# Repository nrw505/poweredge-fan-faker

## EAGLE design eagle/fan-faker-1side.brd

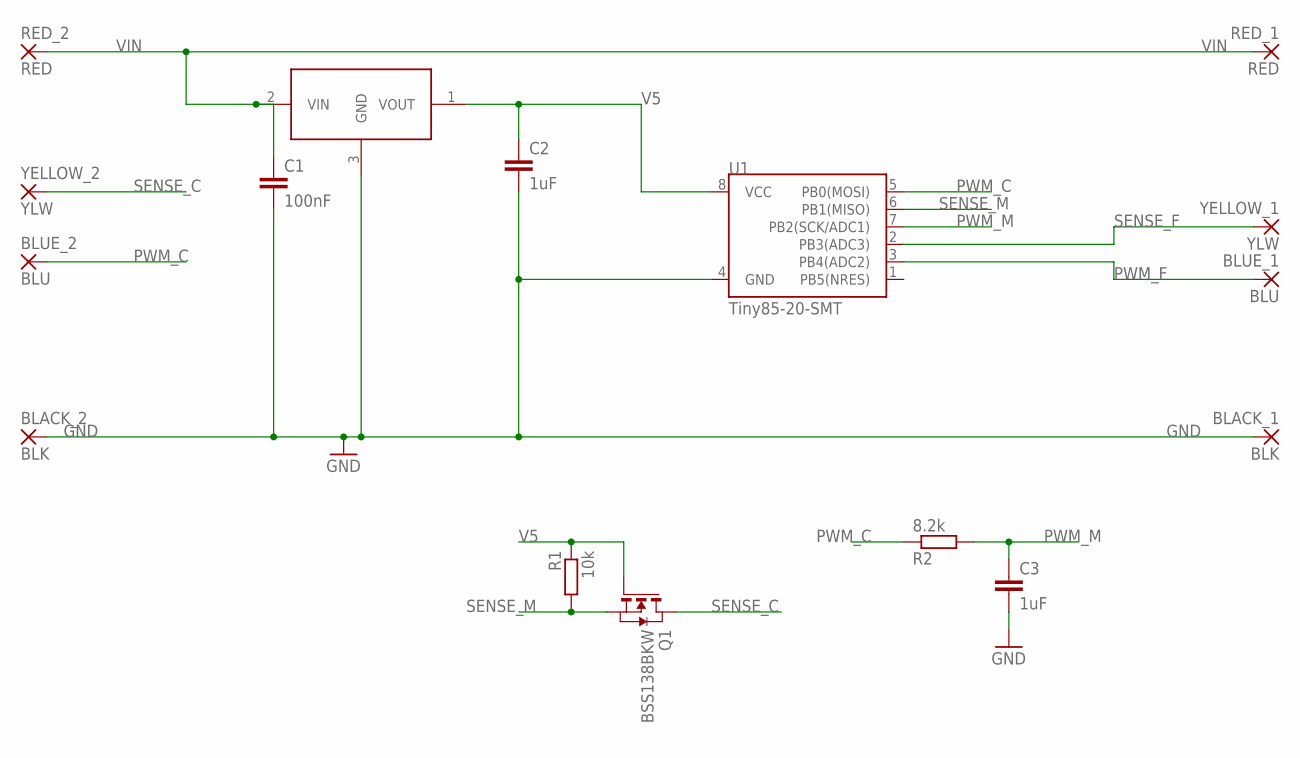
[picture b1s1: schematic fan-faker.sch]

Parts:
BLACK_1, BLACK_2: BLK; 2,54/1,0
BLUE_1, BLUE_2: BLU; 2,54/1,0
C1: 100nF; C0805K
C2, C3: 1uF; C0805K
Q1: BSS138BKW; SOT323
R1: 10k; R0805
R2: 8.2k; R0805
RED_1, RED_2: RED; 2,54/1,0
U1: Tiny85-20-SMT; SO08-EIAJ
U$2: LM3480; SOT23
YELLOW_1, YELLOW_2: YLW; 2,54/1,0

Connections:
GND: BLACK_1.1, BLACK_2.1, C1.2, C2.2, C3.2, U1.4 (GND), U$2.3 (GND)
PWM_C: BLUE_2.1, R2.1, U1.5 (PB0(MOSI))
PWM_F: BLUE_1.1, U1.3 (PB4(ADC2))
PWM_M: C3.1, R2.2, U1.7 (PB2(SCK/ADC1))
SENSE_C: Q1.1 (D), YELLOW_2.1
SENSE_F: U1.2 (PB3(ADC3)), YELLOW_1.1
SENSE_M: Q1.3 (S), R1.2, U1.6 (PB1(MISO))
V5: C2.1, Q1.2 (G), R1.1, U1.8 (VCC), U$2.1 (VOUT)
VIN: C1.1, RED_1.1, RED_2.1, U$2.2 (VIN)

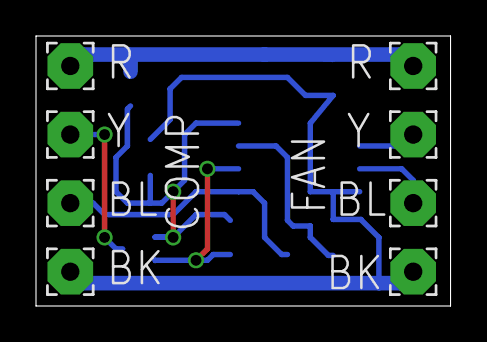
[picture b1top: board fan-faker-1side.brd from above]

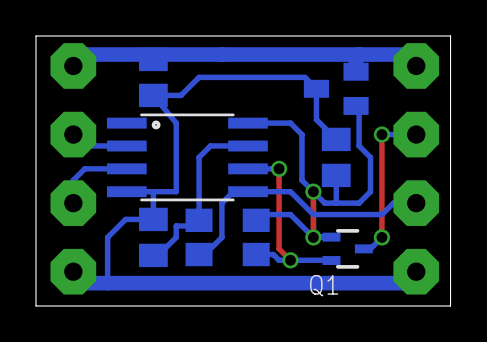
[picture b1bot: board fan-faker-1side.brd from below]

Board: 2 copper layers, 23.0 x 15.0 mm, 16 parts (8 on the bottom side), 9 nets.

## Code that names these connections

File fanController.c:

/* -*- mode: c++; c-basic-offset: 2; -*- */

#include <alloca.h>
#include <string.h>

#include <avr/io.h>
#include <avr/interrupt.h>

// Don't forget to program fuses: this code is expecting the system clock
// to be running at 8 MHz. It was tested on a chip with:
// lfuse=0xe2 hfuse=0xdd efuse=0xff

FUSES = {
  // 8MHz Internal RC Osc., Slow Startup
  .low = (FUSE_SUT0 & FUSE_CKSEL0 & FUSE_CKSEL2 & FUSE_CKSEL3),
  // Enable SPI Programming, Brownout detector hits at 2.7V
  .high = (FUSE_SPIEN & FUSE_BODLEVEL1),
  // No need for self programming
  .extended = EFUSE_DEFAULT,
};


// UNCONNECTED  is pin 1 / PB5 / -RESET
// PIN_SENSE_F  is pin 2 / PB3 / PCINT3
// PIN_PWM_F    is pin 3 / PB4 / OC1B
// PIN_PWM_C    is pin 5 / PB0 / PCINT0
// PIN_SENSE_C  is pin 6 / PB1
// PIN_PWM_M    is pin 7 / PB2 / ADC1 / PCINT2

// PIN_SENSE_F is the open-collector input from the fan: 2 low pulses
//             per revolution

// PIN_PWM_F   is the PWM control to the fan: high duty cycle = fast,
//             low duty cycle = slow

// PIN_PWM_C   is the PWM control from the computer: high duty cycle =
//             wants fast, low duty cycle = wants slow
// PIN_PWM_M   is the PWM control from the computer, run through a low
//             pass filter to get an analog input.
// Note that both these inputs are driven from the same control line,
// but PIN_PWM_C is unfiltered and PIN_PWM_M is filtered

// PIN_SENSE_C is the open-collector sense line to the computer: we use
//             this to lie to the computer about how fast the fan is
//             going (2 low pulses per revolution, 50% duty cycle)


// PWM_COUNTER is used to set the frequency of the PWM signal we send
// to the fan. The spec from Intel says this should be ~25 kHz -
// setting OCR1C to 165, and using the fast peripheral clock /16 to
// drive timer1 gives us 24.5 kHz

#define PWM_COUNTER 165

#define PWM_INPUT_ACCUM_SAMPLES 256
// Ticks here are 1/4000 of a sec, so 16 ticks between samples means 250
// samples a second, or averaging over just over a second
#define PWM_INPUT_TICKS_PER_SAMPLE 16

#define TICKS_PER_FAN_SPEED_CHECK 2000
// Update the fan speed twice a second

volatile uint8_t outSense;
volatile uint8_t lastPwm;
volatile uint8_t lastPwmHighTime;
volatile uint8_t lastPwmLowTime;

volatile uint16_t ticks; // 1 tick per overflow of timer0 == 256 uS
volatile uint32_t secs;  // ideally this is actual seconds.

volatile uint16_t pwmInputAccumulator;

volatile uint8_t fanStartup;
volatile uint8_t checkFanControl;

void setFanPercentage(int pct) {
  OCR1B = (PWM_COUNTER * pct) / 100;
}

void setFanFullSpeed() {
  // Set PB4 Input/HighZ

  // Fan should sense this and switch to full speed / uncontrolled
  // This is used to allow some fans which cannot start when PWM control
  // is asking for too low a speed.

  // Dell BMC also uses it to indicate system fault that requires full
  // speed on all fans
  
  PORTB &= ~(_BV(PB4));
  DDRB &= ~(_BV(DDB4));

  // Disconnect from timer1 PWM generation
  GTCCR &= ~(_BV(COM1B0) | _BV(COM1B1));
}

void setFanPWM() {
  // Set PB4 output
  DDRB |= _BV(DDB4);

  // Connect to timer1 PWM generation
  GTCCR |= _BV(COM1B1);
}

void setupTimer0() {
  ticks = 0;
  secs = 0;

  // CTC Mode: count from 0 to OCR0A and reset to 0
  // clock source is sys clock/8 (or 1MHz)
  // Set OCR0A to 250, so tick is 1MHZ/250 (or 4kHz)
  // Enable interrupt on OCR0A match, so timer interrupt at 4 kHz
  
  // Tick count * 250 + read of TCNT0 gives time in microseconds since ticks
  // wrapped
  
  TCCR0A = _BV(WGM01); 
  TCCR0B = _BV(CS01);
  TCNT0 = 0;
  OCR0A = 250;

  TIMSK |= _BV(OCIE0A);

}

void setupTimer1() {
  // Set PCKE and PLLE

  PLLCSR = _BV(PCKE) | _BV(PLLE);
  
  // Set clock sel = PCK/16, OCR1C to 165 (25kHz ish)
  // PWM1A = off, PWM1B = on
  TCCR1 = _BV(CS12) | _BV(CS10);
  GTCCR = (GTCCR & (_BV(TSM) | _BV(PSR0))) | _BV(PWM1B) | _BV(COM1B1);

  OCR1C = PWM_COUNTER;

  // Set PWM B output to 33%
  setFanPercentage(33);
}

void setupPinInterrupts() {
  PCMSK = _BV(PCINT3) | _BV(PCINT2);
  GIMSK |= _BV(PCIE);
}

void setupADC() {
  // Set left-adjusted (this way we can just read
  // ADCH and get an 8-bit reading)
  // Set ADC source to ADC1 / PB2
  // Set VREF to Vcc
  ADMUX = _BV(ADLAR) | _BV(MUX0);
  
  // Enable ADC
  // Set prescaler to make ADC clock to 125kHz (sysclk / 64)
  // Enable ADC Interrupt on conversion complete
  ADCSRA = _BV(ADEN) | _BV(ADIE) | _BV(ADPS2) | _BV(ADPS1);

  // Disable digital input buffer for PB2
  DIDR0 = _BV(ADC1D);

}

void setup() {
  // Set PB4 to output
  // PB1 stays input (HI-Z) because it's supposed to be wired-OR
  DDRB = _BV(DDB4);

  // PB3 is an input, write 1 to PORTB(3) to enable internal pull-up
  PORTB |= _BV(PB3);

  // disable interrupts
  cli();
  
  setupTimer0();
  setupTimer1();
  setupPinInterrupts();
  setupADC();

  checkFanControl = 0;
  fanStartup = 1;
  setFanFullSpeed();
  
  // now everything's set up, enable interrupts
  sei();
}

// pwmInput is 0 for 0% duty cycle, linear up to 255 for 100% duty cycle
// return a percentage duty cycle to set on the fan control output
int calculateFanPercentage(uint8_t pwmInput) {
  if (pwmInput == 0)
    return 0;
  if (pwmInput < 8)
    return 0 + ((pwmInput - 0) * 5 / 8);
  if (pwmInput < 192)
    return 5 + ((pwmInput - 8) * 10 / (192 - 8));
  if (pwmInput < 224)
    return 15 + ((pwmInput - 192) * 15 / (224 - 192));
  return 30 + ((pwmInput - 224) * 70 / (256 - 224));
}

void loop() {
  if (fanStartup) {
    if (secs > 0) {
      setFanPWM();
      fanStartup = 0;
      checkFanControl = 1;
    }
  } else {
    if (checkFanControl) {
      uint8_t avgPwm = pwmInputAccumulator / PWM_INPUT_ACCUM_SAMPLES;

      int tmp = calculateFanPercentage(avgPwm);
      setFanPercentage(tmp);
      checkFanControl = 0;
    }
  }
}

int main(void) {
  setup();
  while (1) {
    loop();
  }
}

ISR(PCINT0_vect) {
  uint8_t val = PINB;

  uint8_t in_fan_s = val & _BV(PB3);
  uint8_t in_pwm_c = val & _BV(PB2);

  if (in_fan_s != 0x00) {
    if (!outSense) {
      // Set PB1 to High-Z and let the pullup do it's job
      val &= ~(_BV(PB1));
      DDRB &= ~(_BV(DDB1));
      outSense = 1;
    }
  } else {
    if (outSense) {
      // Set PB1 to output LOW
      val &= ~(_BV(PB1));
      DDRB |= _BV(DDB1);
      outSense = 0;
    }
  }

  if (in_pwm_c && !lastPwm) {
    lastPwm = in_pwm_c;
  } else if (!in_pwm_c && lastPwm) {
    lastPwm = in_pwm_c;
  }

  // Keep PB3 high to keep the pullup on PB3's input enabled!
  val |= _BV(PB3);

  PORTB = val;
}

ISR(TIMER0_COMPA_vect) {
  uint16_t newTicks = ticks + 1;
  if (newTicks == 4000) {
    secs++;
    newTicks = 0;
  }
  ticks = newTicks;

  if (newTicks % PWM_INPUT_TICKS_PER_SAMPLE == 0) {
    // Start an ADC sample
    ADCSRA |= _BV(ADSC);
  }

  if (newTicks % TICKS_PER_FAN_SPEED_CHECK == 0) {
    checkFanControl = 1;
  }
}

ISR(ADC_vect) {
  uint8_t newReading = ADCH;
  pwmInputAccumulator = pwmInputAccumulator - (pwmInputAccumulator / PWM_INPUT_ACCUM_SAMPLES) + newReading;
}

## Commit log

2015-06-28 Should get this into version control...
2015-06-28 Implement speed scaling curve, which is the whole point of this thing
2015-06-28 Pull shared AVR/arduino makefile into repo
2015-06-29 Add licencing before I push this to github
2015-06-29 Remove timer debug from PB0, it's actually supposed to be an input
2015-06-29 Works better if the input from an open-collector driver has a pull-up enabled
2015-06-29 note down what fuse settings should be
2015-06-29 Set fuse values in source, even if we don't automatically program them from there yet
2015-06-30 Don't clear the pullup on PB3
2015-07-01 add makefile targets to write out the fuses that are specified in source
2015-07-03 Added schematic and board layouts

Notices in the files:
parts and their libraries:
SparkFun-DigitalIC: Licensing: Creative Commons ShareAlike 4.0 International - https://creativecommons.org/licenses/by-sa/4.0
